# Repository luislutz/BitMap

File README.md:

# BitMap
Multifunction Eurorack Module with 8 Bit parallel ADC and DAC in the Heart. Main selling points:
- most versatile Bitcrusher in Eurorack with passive LPF
- infinite Sample and Hold with slew, works with 1v/oct pitch CV!
- Halftone Chromatic, Chromatic and weird scales Quantizer (every 2nd, 4th, 8th, 16th)
- inspiring Drum/Gate Sequencer with 8 Channels
- VCA and Ringmodulator
- White Noise, 8 types of digital noise and processed White Noise (Bitcrushed, Sample Rate reduced and Filtered to your taste)

## Features and Functions:

Conversion of analog voltage in 8 Bit digital value
Possibility of swapping individual bits and switching them off manually, 
aswell as removing the bits in order via the voltage controlled Bitcrush-Knob
Reconversion of digital 8 Bit value in analog voltage

ADC and DAC can be used as seperate units with the same clock (onboard pulsegenerator or external trigger/gates):

ADC: 1 analog input, 8 digital bit outputs derived from the input voltage (Gates), additional Clip output wich goes high when the input voltage is bigger than the ADC range, this produces hard clipping

DAC: 8 digital inputs (Gates), 1 analog output derived from the digital input values. Possibitlity to set the refence voltage of the DAC externally via an analog gain input, works as a VCA with unipolar Voltage or Ringmodulator with bipolar Voltage

Normalled white noise to the analog input of the ADC aswell as a seperate unprocessed noise output. This gives direct access to 9 flavours of Digital Noise at the ADC Bit outputs and Clip output and a processed white noise at the analog output of the DAC without having to add some other modules or cables. The processed white noise can of course be bitcrushed and samplerate reduced as you wish aswell. Random Voltages in S and Hold style are achievable too with really slow clock rate. With the passive Slew limiter (LPF) at the output the noise can be filtered too and it is possible to slew the Sample and Hold Voltages.

Because the value of the incoming analog voltage is stored in Digital realm. The module does act as a Sample and Hold circuit with infinite holding time and zero voltage drop. Using this module to sample and hold pitch CV is no problem.

The coolest feature by far is the precise mapping of the 256 steps in 8 Bit to the V/Oct scale at the analog input and output. To set the module up for quantizing Pitch CV, just turn the input and output level knobs all the way up. Now a Voltage of 0 (C3) at the input equals a digital word of 10000000, C#3 would be 10000010, D3 = 10000100, D#3 = 10000110 and so on. one Sem,itone equals two steps in the Digital realm. So the minimum voltage value will be -5.33V (00000000, G#-3) and the maximum voltage is 5.25 (11111110, D#8). The Quantizing range is therefor over 10 Octaves of Notes. There are many possibilities for quantizing pitch cv. For Chromatic quantizing, disable the lowest value bit. if you want everey 2nd, 4th, 8th semitone and so on,disable more bits or make any weird combination of bits to make weird scales that are impossible using a normal quantizer. Normal scales like Major Minor or Phrigyian are not so easy to replicate with this module.

## Different Use Cases:

- Voltage controlled Bitreducing of CV and Audio signals
- Voltage controlled Reducing of Sample Rate for CV and Audio Signals (S&H)
- Random Voltage and Gate Source
- Sequencing Drums with mutes (up to 9 channels)
- Quantizing of pitch CV (Chromatic and unusal scales)
- VCA and Ringmodulator (after AD->DA Conversion on the Output)
- Sequencer for pitch CV
- infinite Sample and Hold with external trigger
- Pitch Sequence Transformation to related, but different Sequences
- Slew and Low pass filtering of output with switchable range (passive)
- Strange Wavefolder (swapping or switching individula bits of Audio)
- Distortion (hardclipping at 10vpp)
- Noise source (1 unprocessed Noise white noise outoput, 9 times digital noise with different flavours, and one 8 bit white noise processable with Bitmap as you wish) 
- Compatible with Leibniz system from Xaoc via Leibniz headers on the back of the module!

## Building Instructions:

This is no easy build! Althought it is mostly throughhole, the Module is really packed with Components and ICs.
The hardest part is to solder the 0603 SMD Resistors and keep them unharmed during the rest of the soldering

Start with the 0603 SMD resistors on the backside of the front PCB!

Using Leibniz Subsystem:
There are 9 Jumpers on the front PCB. if you solder these jumpers, the optional connectors for the Leibniz subsystem are bridged and wont be needed anymore. If you want to use the Leibniz subsystem now or in the Future, please make sure you dont solder the jumpers and solder the connectors for the Leibniz subsystem.
Before soldering the Thonkiconn Jacks (3.5mm mono jacks) make sure to solder the Leibniz Headers first. Make sure the pins of the Leibniz connector is flush with the Frontside of the PCB, that way they dont interfere with the 3.5mm Mono Jacks on the oter side of the PCB.

After you have made your decision, start putting everything else in by starting with the most slim parts (Resistors, diodes) and end with the Biggest parts (Elko Caps, trimmers, pin headers)
Solder the panel components with the panel already mounted on them to make sure the parts will align with the holes in the PCB Panel

## Calibraton:

Set Up: 
- SampleRate Knob ~70% to the right
- Bitcrush Knob 100% to the left
- Input Level Knob 100% to the left
- CV Scale Knob 100% to the left
- Slew Pot 100% to the left
- Output Pot 100% to the right
- All individual Bit Buttons are not pressed, e.g. Bits are all active!

there are 6 calibrating trimpotentiometers in total to be adjusted:

1. Input Offset trim RV5 10K:
Turn the Input Level Knob on the Panel completely to the left first. Listen to the Noise Output Jack. Turn the Noise Trim Potentiometer completely down, so that there is absolutely no Nosie left at the Noise Output Jack. This should result in less flickering of the Bit LEDS on the Panel (This is really important). Now youre set for precise calibration. Adjust the Input Offset Trim Potentiometer so that the LEDs light up with this pattern from left to right without flickering: 00000001 (EG Only BIT8 is set active)

2. Input Scale trim RV4 10K:
Take a constant voltage source with exactly 5V (coming from a sequencer or similar) and plug it in the analog voltage input. Turn the Input Level Knob on the Frontpanel completely up (100% to the right). Adjust the Input Scale Trim Potentiometer so that LEDs light up with this pattern from left to right: 00011111    ---> repeat Step 1. and Step 2. until it stays at the correct LED-Pattern with the corresponding input voltage and no jitter.

3. Output Offset trim RV6 2K:
Keep the precise 5V source plugged in. Turn the Input Level Knob on the panel to zero again. Connect the output to a Voltage Meter or to the V/Oct input of an Oscillator that is already well calibrated to 1V/Oct. Make sure you see the Pattern 00000001 on the LEDs. Adjust the Output Offset Trim until the Output Voltage equals excactly 0V or your oscillator doesnt change pitch when unpluuging the cable from the V/Oct input (should be the case for a good calibrated VCO with 0V at the cable)

4. Output Scale trim RV9 2K:
Keep the precise 5V source plugged in. Turn the Input Voltage Knob on the Panel to max (100% to the right). Now the LED-Pattern should be (00011111) again. Leave the Analog Voltage Output connected to the oscillator or the Voltage Meter. Adjust the Output Scale Trim until the output matcehs excactly 5 volts or the Oscillator is playing 5 Octaves above when compared to Step 3.
--> your Input and Output Scales and Offsets are now set correctly to 1V/Oct

5. Max Sample Rate trim RV12 2K:
Feed a Sinewave into the analog input Jack. Listen to the output of the Module. Turn the Sample Rate Knob on the panel to max value (100% to the right). Adjust the Sample Rate Trim to minimal noise on the output (Hint: if the sample rate just exceeds audible range its perfect there). if the Sample Rate trim is set to high. The ADC stalls when turning the SR pot all the way to the Right, you can unstall the ADC by turning it quite down, but its better to set that trimmer in a way that the ADC doest lock at all when the Sample Rate Pot is at its max Setting (100% to the right)

6. Noise Level trim RV3 100K: 
Turn the Input Level Knob again completely to the left. Now turn the Noise trimpot up until there is a slight flickering at the LEDs on the Panel (because the dac is very quickly switching States because of increased signal noise at the input). Turn it slightly back so that the flickering stops. Noise level is now set to Max Level without interference to the input Voltage. Any higher and the Readings of Voltages to the Analog Voltage input get inprecise and noisy. For max precision on Pitch CV you can even turn the noise trim completely down :) if your more after noisy behaviour it doesnt matter that much and you can turn up the noise quite abit :D

if you have any questions regarding the building or calibration Process you can write me an email to luis.lutz95@gmail.com 

Thanks for thaking the challenge to build one of these!!!

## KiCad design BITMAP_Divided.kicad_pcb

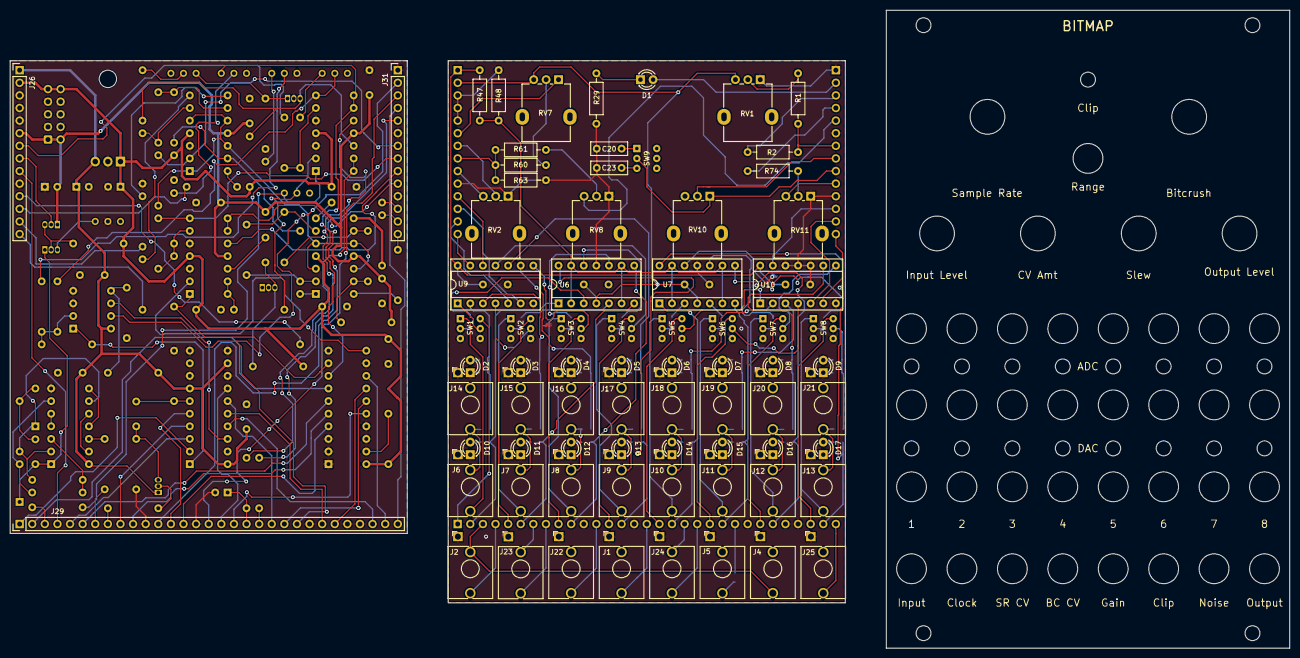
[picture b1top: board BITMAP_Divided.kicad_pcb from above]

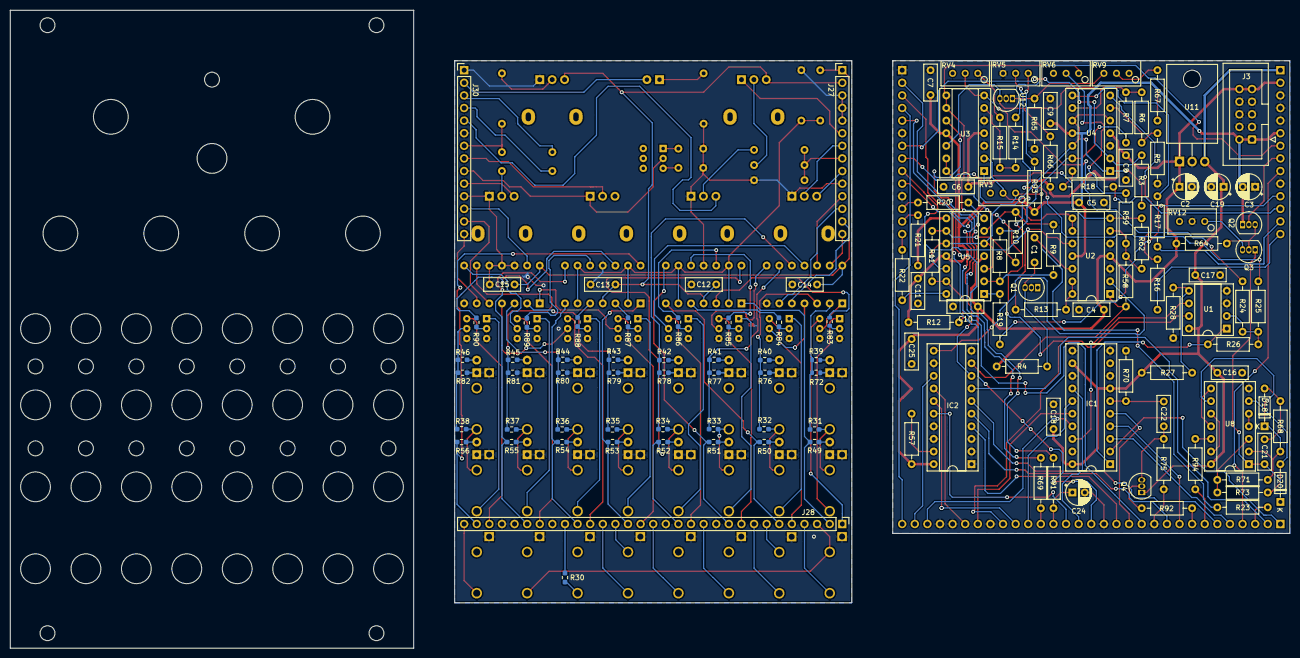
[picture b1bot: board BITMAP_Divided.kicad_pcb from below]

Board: 2 copper layers, 257.8 x 128.5 mm, 208 parts (134 on the bottom side), 217 nets.

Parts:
C1, C4, C5, C6, C7, C8, C9, C10, C11, C12, C13, C14, C15, C16, C17, C18, C25: 100n; C_Rect_L7.2mm_W2.5mm_P5.00mm_FKS2_FKP2_MKS2_MKP2
C2, C3, C19, C24: 10u; CP_Radial_D5.0mm_P2.50mm
C20: 68n; C_Rect_L7.2mm_W2.5mm_P5.00mm_FKS2_FKP2_MKS2_MKP2
C21: 2.2n; C_Rect_L7.2mm_W2.5mm_P5.00mm_FKS2_FKP2_MKS2_MKP2
C22: 1n; C_Rect_L7.2mm_W2.5mm_P5.00mm_FKS2_FKP2_MKS2_MKP2
C23: 680n; C_Rect_L7.2mm_W2.5mm_P5.00mm_FKS2_FKP2_MKS2_MKP2
D1, D2, D3, D4, D5, D6, D7, D8, D9, D10, D11, D12, D13, D14, D15, D16, D17: LED; LED_D3.0mm
D18, D20: 1N4148; D_DO-35_SOD27_P7.62mm_Horizontal
IC1: ADC0820CCN; DIP-20_W7.62mm_Socket
IC2: DAC0830LJ; DIP-20_W7.62mm_Socket
J1: Bitcrush CV; Jack_3.5mm_QingPu_WQP-PJ398SM_Vertical_CircularHoles
J2: Signal Input; Jack_3.5mm_QingPu_WQP-PJ398SM_Vertical_CircularHoles
J3: Eurorack Power Header; IDC-Header_2x05_P2.54mm_Vertical
J4: Noise Output; Jack_3.5mm_QingPu_WQP-PJ398SM_Vertical_CircularHoles
J5: Clip Output; Jack_3.5mm_QingPu_WQP-PJ398SM_Vertical_CircularHoles
J6: Bit 0 Input; Jack_3.5mm_QingPu_WQP-PJ398SM_Vertical_CircularHoles
J7: Bit 1 Input; Jack_3.5mm_QingPu_WQP-PJ398SM_Vertical_CircularHoles
J8: Bit 2 Input; Jack_3.5mm_QingPu_WQP-PJ398SM_Vertical_CircularHoles
J9: Bit 3 Input; Jack_3.5mm_QingPu_WQP-PJ398SM_Vertical_CircularHoles
J10: Bit 4 Input; Jack_3.5mm_QingPu_WQP-PJ398SM_Vertical_CircularHoles
J11: Bit 5 Input; Jack_3.5mm_QingPu_WQP-PJ398SM_Vertical_CircularHoles
J12: Bit 6 Input; Jack_3.5mm_QingPu_WQP-PJ398SM_Vertical_CircularHoles
J13: Bit 7 Input; Jack_3.5mm_QingPu_WQP-PJ398SM_Vertical_CircularHoles
J14: Bit 0 Output; Jack_3.5mm_QingPu_WQP-PJ398SM_Vertical_CircularHoles
J15: Bit 1 Output; Jack_3.5mm_QingPu_WQP-PJ398SM_Vertical_CircularHoles
J16: Bit 2 Output; Jack_3.5mm_QingPu_WQP-PJ398SM_Vertical_CircularHoles
J17: Bit 3 Output; Jack_3.5mm_QingPu_WQP-PJ398SM_Vertical_CircularHoles
J18: Bit 4 Output; Jack_3.5mm_QingPu_WQP-PJ398SM_Vertical_CircularHoles
J19: Bit 5 Output; Jack_3.5mm_QingPu_WQP-PJ398SM_Vertical_CircularHoles
J20: Bit 6 Output; Jack_3.5mm_QingPu_WQP-PJ398SM_Vertical_CircularHoles
J21: Bit 7 Output; Jack_3.5mm_QingPu_WQP-PJ398SM_Vertical_CircularHoles
J22: Sample Rate CV; Jack_3.5mm_QingPu_WQP-PJ398SM_Vertical_CircularHoles
J23: Ext Clock Input; Jack_3.5mm_QingPu_WQP-PJ398SM_Vertical_CircularHoles
J24: External Voltage Reference Input; Jack_3.5mm_QingPu_WQP-PJ398SM_Vertical_CircularHoles
J25: Signal Output; Jack_3.5mm_QingPu_WQP-PJ398SM_Vertical_CircularHoles
J26, J31: Conn_01x14_Male; PinHeader_1x14_P2.54mm_Vertical
J27, J30: Conn_01x14_Female; PinHeader_1x14_P2.54mm_Vertical
J28: Conn_01x31_Female; PinHeader_1x31_P2.54mm_Vertical
J29: Conn_01x31_Male; PinHeader_1x31_P2.54mm_Vertical
Q1, Q3, Q4: BC547; TO-92_Inline
Q2: BC557; TO-92_Inline
R1, R3, R15: 100K; R_Axial_DIN0207_L6.3mm_D2.5mm_P10.16mm_Horizontal
R2, R60, R61: 47K; R_Axial_DIN0207_L6.3mm_D2.5mm_P10.16mm_Horizontal
R4: 200K; R_Axial_DIN0207_L6.3mm_D2.5mm_P10.16mm_Horizontal
R5, R6, R7, R8, R9, R10, R11, R12, R16, R17, R18, R19, R20, R21, R22: 5.1K; R_Axial_DIN0207_L6.3mm_D2.5mm_P10.16mm_Horizontal
R13, R23, R29, R69, R75, R92, R94: 1K; R_Axial_DIN0207_L6.3mm_D2.5mm_P10.16mm_Horizontal
R14: 220K; R_Axial_DIN0207_L6.3mm_D2.5mm_P10.16mm_Horizontal
R24, R25, R26, R27, R28, R47, R48, R57, R58, R65, R66, R67, R70, R71, R91: 10K; R_Axial_DIN0207_L6.3mm_D2.5mm_P10.16mm_Horizontal
R30, R31, R32, R33, R34, R35, R36, R37, R38, R40, R41, R42, R43, R44, R45, R46, R49, R50, R51, R52, R53, R54, R55, R56, R84, R85, R86, R87, R88, R89, R90: 1K; R_0603_1608Metric_Pad0.98x0.95mm_HandSolder
R39, R83: 1K; R_0603_1608Metric
R59, R62: 20K; R_Axial_DIN0207_L6.3mm_D2.5mm_P10.16mm_Horizontal
R63: 1.8K; R_Axial_DIN0207_L6.3mm_D2.5mm_P10.16mm_Horizontal
R64: 1M; R_Axial_DIN0207_L6.3mm_D2.5mm_P10.16mm_Horizontal
R68: 680R; R_Axial_DIN0207_L6.3mm_D2.5mm_P10.16mm_Horizontal
R72: 10K; R_0603_1608Metric
R73: 22K; R_Axial_DIN0207_L6.3mm_D2.5mm_P10.16mm_Horizontal
R74: 470R; R_Axial_DIN0207_L6.3mm_D2.5mm_P10.16mm_Horizontal
R76, R77, R78, R79, R80, R81, R82: 10K; R_0603_1608Metric_Pad0.98x0.95mm_HandSolder
R93: 33K; R_Axial_DIN0207_L6.3mm_D2.5mm_P10.16mm_Horizontal
RV1, RV2, RV7, RV8, RV11: 100K; Potentiometer_Alpha_RD901F-40-00D_Single_Vertical
RV3: 100K; Potentiometer_Bourns_3296W_Vertical
RV4, RV5: 10K; Potentiometer_Bourns_3296W_Vertical
RV6, RV9, RV12: 2K; Potentiometer_Bourns_3296W_Vertical
RV10: 10K; Potentiometer_Alpha_RD901F-40-00D_Single_Vertical
SW1: Bit 0 Mute Switch; 7x7Switch
SW2: Bit 1 Mute Switch; 7x7Switch
SW3: Bit 2 Mute Switch; 7x7Switch
SW4: Bit 3 Mute Switch; 7x7Switch
SW5: Bit 4 Mute Switch; 7x7Switch
SW6: Bit 5 Mute Switch; 7x7Switch
SW7: Bit 6 Mute Switch; 7x7Switch
SW8: Bit 7 Mute Switch; 7x7Switch
SW9: Slew Range Switch; 7x7Switch
U1: MCP6002-xP; DIP-8_W7.62mm_Socket
U2, U3, U4, U5: TL074; DIP-14_W7.62mm_Socket
U6, U7: LM324; DIP-14_W7.62mm_Socket
U8: 4069; DIP-14_W7.62mm_Socket
U9, U10: 4066; DIP-14_W7.62mm_Socket
U11: L7805; TO-220-3_Horizontal_TabDown
U12: TL431LP; TO-92_Inline

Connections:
+5V_Back: C16.1, C17.1, C18.2, C19.1, IC1.7, IC1.12, IC1.20, J26.1, Q4.1, R27.2, U1.8, U8.14, U11.3
+5V_Front: C14.1, C15.1, J27.1, R47.2, U9.14, U10.14
+12V_Back: C2.1, C4.1, C6.1, C8.1, C10.1, C25.2, IC2.20, J3.9, J3.10, J26.2, R4.2, R57.2, R64.2, R66.2, U2.4, U3.4, U4.4, U5.4, U11.1
+12V_Front: C12.1, C13.1, J27.2, RV1.3, RV7.3, U6.4, U7.4
-12V_Back: C3.2, C5.2, C7.2, C9.2, C11.2, J3.1, J3.2, J26.6, Q2.1, R12.1, R93.2, U2.11, U3.11, U4.11, U5.11
-12V_Front: J27.6, RV7.1
B0_Back: IC2.7, J29.2
B0_Front: J28.2, R49.2, U6.1
B1_Back: IC2.6, J29.6
B1_Front: J28.6, R50.2, U6.7
B2_Back: IC2.5, J29.10
B2_Front: J28.10, R51.2, U6.8
B3_Back: IC2.4, J29.14
B3_Front: J28.14, R52.2, U6.14
B4_Back: IC2.16, J29.18
B4_Front: J28.18, R53.2, U7.1
B5_Back: IC2.15, J29.22
B5_Front: J28.22, R54.2, U7.7
B6_Back: IC2.14, J29.26
B6_Front: J28.26, R55.2, U7.8
B7_Back: IC2.13, J29.30
B7_Front: J28.30, R56.2, U7.14
Bitcrush_Back: J31.7, R3.2, U4.2
Bitcrush_Back_Jack1: J29.16, J31.3
Bitcrush_Front: J30.7, R1.1, R2.1
Bitcrush_Front_Jack1: J1.2, J28.16
Bitcrush_Front_Jack2: J30.3, R2.2
Clip_Back: J29.23, J31.2, U1.7
Clip_Front_Jack: J28.23, R30.1
Clip_Front_LED: D1.2, J30.2
Clk: C22.2, IC1.6, R70.2
Clock1_Back: J29.7, R94.1
Clock1_Front: J23.3, J28.7
Clock2_Back: J29.8, R92.1
Clock2_Front: J23.2, J28.8
D0_Back: IC1.2, J29.1
D0_Front: J28.1, SW1.4
D1_Back: IC1.3, J29.5
D1_Front: J28.5, SW2.4
D2_Back: IC1.4, J29.9
D2_Front: J28.9, SW3.4
D3_Back: IC1.5, J29.13
D3_Front: J28.13, SW4.4
D4_Back: IC1.14, J29.17
D4_Front: J28.17, SW5.4
D5_Back: IC1.15, J29.21
D5_Front: J28.21, SW6.4
D6_Back: IC1.16, J29.25
D6_Front: J28.25, SW7.4
D7_Back: IC1.17, J29.29
D7_Front: J28.29, SW8.4
GND_Back: C2.2, C3.1, C4.2, C5.1, C6.2, C7.1, C8.2, C9.1, C10.2, C11.1, C16.2, C17.2, C18.1, C19.2, C24.2, C25.1, IC1.8, IC1.10, IC1.11, IC1.13, IC2.1, IC2.2, IC2.3, IC2.10, IC2.12, IC2.17, IC2.18, J3.3, J3.4, J3.5, J3.6, J3.7, J3.8, J26.3, J26.4, J26.5, J26.10, J29.11, J29.15, J29.24, J29.27, J29.28, J31.1, J31.6, J31.11, Q1.2, R5.2, R28.1, R65.1, R70.1, R75.2, RV5.3, RV12.2, U1.3, U1.4, U2.3, U2.5, U3.3, U3.5, U4.3, U8.7, U11.2, U12.2
GND_Front: C12.2, C13.2, C14.2, C15.2, C20.2, C23.2, D2.1, D3.1, D4.1, D5.1, D6.1, D7.1, D8.1, D9.1, D10.1, D11.1, D12.1, D13.1, D14.1, D15.1, D16.1, D17.1, J1.1, J2.1, J4.1, J5.1, J6.1, J7.1, J8.1, J9.1, J10.1, J11.1, J12.1, J13.1, J14.1, J15.1, J16.1, J17.1, J18.1, J19.1, J20.1, J21.1, J22.1, J23.1, J24.1, J25.1, J27.3, J27.4, J27.5, J27.10, J28.11, J28.15, J28.24, J28.27, J28.28, J30.1, J30.6, J30.11, R29.2, R48.1, R63.1, R72.1, R76.1, R77.1, R78.1, R79.1, R80.1, R81.1, R82.1, RV1.1, RV2.1, RV8.1, RV11.1, SW1.3, SW1.6, SW2.3, SW2.6, SW3.3, SW3.6, SW4.3, SW4.6, SW5.3, SW5.6, SW6.3, SW6.6, SW7.3, SW7.6, SW8.3, SW8.6, U6.11, U7.11, U9.7, U10.7, U10.10, U10.11, U10.12
In_Back: J26.7, R14.2
In_Back1: J26.9, J29.4
In_Front: J27.7, RV2.2
In_Front1: J2.2, J28.4
In_Front2: J27.9, RV2.3
unnamed: C1.1, Q1.3, R4.1
unnamed: C1.2, U2.12
unnamed: C20.1, SW9.1
unnamed: C21.1, D20.1, Q3.1, U8.1
unnamed: C21.2, D18.2, R68.2
unnamed: C22.1, Q4.3, R75.1
unnamed: C23.1, SW9.3
unnamed: D1.1, R29.1
unnamed: D2.2, R39.1
unnamed: D3.2, R40.1
unnamed: D4.2, R41.1
unnamed: D5.2, R42.1
unnamed: D6.2, R43.1
unnamed: D7.2, R44.1
unnamed: D8.2, R45.1
unnamed: D9.2, R46.1
unnamed: D10.2, R49.1
unnamed: D11.2, R50.1
unnamed: D12.2, R51.1
unnamed: D13.2, R52.1
unnamed: D14.2, R53.1
unnamed: D15.2, R54.1
unnamed: D16.2, R55.1
unnamed: D17.2, R56.1
unnamed: D18.1, R68.1, R71.2, U8.2, U8.9
unnamed: D20.2, R73.1, U8.6
unnamed: IC1.1, R26.1, U1.1
unnamed: IC1.18, U1.6
unnamed: IC2.9, R58.2, U2.1
unnamed: IC2.11, U2.2
unnamed: IC2.19, R57.1
unnamed: J5.2, R30.2
unnamed: J6.2, SW1.1
unnamed: J7.2, SW2.1
unnamed: J8.2, SW3.1
unnamed: J9.2, SW4.1
unnamed: J10.2, SW5.1
unnamed: J10.3, J18.2, R35.1
unnamed: J11.2, SW6.1
unnamed: J11.3, J19.2, R36.1
unnamed: J12.2, SW7.1
unnamed: J12.3, J20.2, R37.1
unnamed: J13.2, SW8.1
unnamed: J13.3, J21.2, R38.1
unnamed: J6.3, J14.2, R31.1
unnamed: J7.3, J15.2, R32.1
unnamed: J8.3, J16.2, R33.1
unnamed: J9.3, J17.2, R34.1
unnamed: Q2.3, Q3.2, R64.1
unnamed: Q3.3, RV12.1
unnamed: Q4.2, R92.2
unnamed: R1.2, RV1.2
unnamed: R3.1, U4.1, U4.5, U4.10, U4.12, U5.3, U5.5, U5.10, U5.12
unnamed: R5.1, R6.2, U4.6
unnamed: R6.1, R7.2, U4.9
unnamed: R7.1, R8.2, U4.13
unnamed: R8.1, R9.2, U5.2
unnamed: R10.1, R11.2, U5.9
unnamed: R9.1, R10.2, U5.6
unnamed: R11.1, R12.2, U5.13
unnamed: R13.1, RV3.2, U3.2
unnamed: R13.2, U2.13, U2.14
unnamed: R14.1, R15.2, U3.6
unnamed: R15.1, RV4.1
unnamed: R16.2, U4.7
unnamed: R17.2, U4.8
unnamed: R18.2, U4.14
unnamed: R19.2, U5.1
unnamed: R20.2, U5.7
unnamed: R21.2, U5.8
unnamed: R22.2, U5.14
unnamed: R23.2, RV3.1, U3.1
unnamed: R24.1, R25.1, R26.2, U1.2
unnamed: R24.2, RV4.2, U3.7
unnamed: R25.2, RV5.2
unnamed: R27.1, R28.2, U1.5
unnamed: R31.2, R39.2, R72.2, U9.2
unnamed: R32.2, R40.2, R76.2, U9.3
unnamed: R33.2, R41.2, R77.2, U9.9
unnamed: R34.2, R42.2, R78.2, U9.10
unnamed: R35.2, R43.2, R79.2, U10.2
unnamed: R36.2, R44.2, R80.2, U10.3
unnamed: R37.2, R45.2, R81.2, U10.9
unnamed: R38.2, R46.2, R82.2, SW8.5
unnamed: R47.1, R48.2, U6.2, U6.6, U6.9, U6.13, U7.2, U7.6, U7.9, U7.13
unnamed: R58.1, R59.1, R62.2, U2.6
unnamed: R59.2, RV6.2
unnamed: R60.2, RV7.2
unnamed: R61.2, RV8.2
unnamed: R65.2, RV9.3, U12.1
unnamed: R66.1, R67.2, U3.12, U12.3
unnamed: R67.1, RV9.2
unnamed: R69.1, U3.10
unnamed: R71.1, R73.2, U8.3
unnamed: R74.2, RV11.2
unnamed: R83.1, U6.3
unnamed: R83.2, SW1.2
unnamed: R84.1, U6.5
unnamed: R84.2, SW2.2
unnamed: R85.1, U6.10
unnamed: R85.2, SW3.2
unnamed: R86.1, U6.12
unnamed: R86.2, SW4.2
unnamed: R87.1, U7.3
unnamed: R87.2, SW5.2
unnamed: R88.1, U7.5
unnamed: R88.2, SW6.2
unnamed: R89.1, U7.10
unnamed: R89.2, SW7.2
unnamed: R90.1, U7.12
unnamed: R90.2, SW8.2
unnamed: R91.2, U3.13, U3.14
unnamed: R93.1, RV5.1
unnamed: R94.2, U8.12
unnamed: SW1.5, U9.1
unnamed: SW2.5, U9.4
unnamed: SW3.5, U9.8
unnamed: SW4.5, U9.11
unnamed: SW5.5, U10.1
unnamed: SW6.5, U10.4
unnamed: SW7.5, U10.8
unnamed: U8.4, U8.5
unnamed: U8.10, U8.13
unnamed: U8.8, U8.11
Noise_Back: J29.3, R23.1
Noise_Front: J2.3, J4.2, J28.3
Out1_Back: J31.8, R62.1, U2.7
Out1_Front: J30.8, RV10.2
Out2_Back: J31.9, U2.10
Out2_Front: J30.9, RV10.1, SW9.2
Out3_Back: J31.10, U2.8, U2.9
Out3_Front: J30.10, RV11.3
Out4_Back: J29.31, J31.4
Out4_Front: J30.4, R74.1
Out5_Front: J25.2, J28.31
Rate_Back: J26.8, Q2.2
Rate_Front: J27.8, R60.1, R61.1, R63.2
Ref1_Back: C24.1, J29.19, R91.1
Ref1_Front: J24.3, J28.19
Ref2_Back: J29.20, R69.2
Ref2_Front: J24.2, J28.20
S0_Back: J26.14, R16.1
S0_Front: J27.14, U9.13
S1_Back: J26.13, R17.1
S1_Front: J27.13, U9.5
S2_Back: J26.12, R18.1
S2_Front: J27.12, U9.6
S3_Back: J26.11, R19.1
S3_Front: J27.11, U9.12
S4_Back: J31.12, R20.1
S4_Front: J30.12, U10.13
S5_Back: J31.13, R21.1
S5_Front: J30.13, U10.5
S6_Back: J31.14, R22.1
S6_Front: J30.14, U10.6
SR_Jack1_Back: J29.12, J31.5
SR_Jack1_Front: J22.2, J28.12
SR_Jack2_Front: J30.5, RV8.3
Vref: IC2.8, RV6.1, U3.8, U3.9

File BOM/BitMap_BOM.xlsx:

Part number on Schematic | Value | Amount | Package | Link for ordering | Comment
Resistors SMD
R31, R32, R33, R34, R35, R36, R37, R38, R83, R83, R85, R86, R87, R88, R89, R90 | 1K | 16 | 0603 SMD | 1K Ohm 1/10W 1% 0603 SMD Chip Resistors (taydaelectronics.com)
R72, R76, R77, R78, R79, R80, R81, R82 | 10K | 8 | 0603 SMD | 10K Ohm 1/10W 1% 0603 SMD Chip Resistors (taydaelectronics.com)
R39, R40, R41, R42, R43, R44, R45, R46 | LED resistors ADC ~3.3K | 8 | 0603 SMD | 4.7K Ohm 1/10W 1% 0603 SMD Chip Resistors (taydaelectronics.com) | Resitor for setting the brightness on the ADC LEDs Running on 5V. Recommended v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
R49, R50, R51. R52, R53, R54, R55, R56 | LED resistors DAC ~75K | 8 | 0603 SMD | 100K Ohm 1/10W 1% 0603 SMD Chip Resistors (taydaelectronics.com) | Resitor for setting the brightness on the DAC LEDs. Running on 12V. Recommended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
Resistors THT
R74 | 470R | 1 | THT 1/4W | Save time Easy Ordering Page for 1/4W 1% Resistors (taydaelectronics.com)
R68 | 680R | 1 | THT 1/4W | Save time Easy Ordering Page for 1/4W 1% Resistors (taydaelectronics.com)
R70, R15, R23, R29, R30, R69, R92, R94 | 1K | 9 | THT 1/4W | Save time Easy Ordering Page for 1/4W 1% Resistors (taydaelectronics.com) | R29 is the Resistor which sets the brightness of the Clip LED running on 5V. Re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
R63 | 1.8K | 1 | THT 1/4W | Save time Easy Ordering Page for 1/4W 1% Resistors (taydaelectronics.com)
R5, R6, R7, R8, R9, R10, R11, R12, R16, R17, R18, R19, R20, R21, R22 | 5.1K | 15 | THT 1/4W | Save time Easy Ordering Page for 1/4W 1% Resistors (taydaelectronics.com)
R24, R26, R25, R27, R28, R47, R48, R57, R58, R65, R66, R67, R71, R75, R91, R93 | 10K | 16 | THT 1/4W | Save time Easy Ordering Page for 1/4W 1% Resistors (taydaelectronics.com)
R59, R62 | 20K | 2 | THT 1/4W | Save time Easy Ordering Page for 1/4W 1% Resistors (taydaelectronics.com)
R73 | 22K | 1 | THT 1/4W | Save time Easy Ordering Page for 1/4W 1% Resistors (taydaelectronics.com)
R2, R60, R61 | 47K | 3 | THT 1/4W | Save time Easy Ordering Page for 1/4W 1% Resistors (taydaelectronics.com)
R15 | 91K | 1 | THT 1/4W | Save time Easy Ordering Page for 1/4W 1% Resistors (taydaelectronics.com)
R1, R3, R95, | 100K | 3 | THT 1/4W | Save time Easy Ordering Page for 1/4W 1% Resistors (taydaelectronics.com)
R4, | 200k | 1 | THT 1/4W | Save time Easy Ordering Page for 1/4W 1% Resistors (taydaelectronics.com)
R14 | 220K | 1 | THT 1/4W | Save time Easy Ordering Page for 1/4W 1% Resistors (taydaelectronics.com)
R64 | 1M | 1 | THT 1/4W | Save time Easy Ordering Page for 1/4W 1% Resistors (taydaelectronics.com)
Capacitors
C4, C5, C6, C7, C8, C9, C10, C11, C12, C13, C14, C15, C16, C17, C18, C25 | 100n | 16 | Ceramic | https://www.taydaelectronics.com/100nf-50v-multilayer-monoli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
C21 | 22n | 1 | Film | 22nF 0.022uF 100V 5% Polyester Film Box Type Capacitor (taydaelectronics.com)
C20 | 68n | 1 | Film | 68nF 0.068uF 100V 5% Polyester Film Box Type Capacitor (taydaelectronics.com)
C1 | 100n | 1 | Film | 100nF 0.1uF 100V 5% Polyester Film Box Type Capacitor (taydaelectronics.com)
C23 | 680n | 1 | Film | 680nF 0.68uF 100V 5% Polyester Film Box Type Capacitor (taydaelectronics.com)
C2, C3, C19, C24 | 10u | 4 | Elko | 10uF 50V 105C Radial Electrolytic Capacitor 5x11mm (taydaelectronics.com)
Diodes
D1 | Clip LED | 1 | LED 3mm round | LED 3mm Red Water Clear Ultra Bright (taydaelectronics.com)
D2, D3, D4, D5, D6, D7, D8, D9 | LEDs ADC | 8 | LED 3mm round | LED 3mm Orange Water Clear (taydaelectronics.com) | Tayda has no yellow LEDs at the moment….
D10, D11, D12, D13, D14, D15, D16, D17 | LEDs DAC | 8 | LED 3mm round | LED 3mm Green Water Clear Super Bright (taydaelectronics.com)
D19 | BAT43 | 1
D18, D20 | 1N4148 | 2 |  | 1N4148 Switching Signal Diode (taydaelectronics.com)
Variable Resistors
RV3 | 100K | 1 | Trim | 100K OHM TRIMMER POTENTIOMETER CERMET 25 TURNS 3296W (taydaelectronics.com)
RV6, RV9, RV12 | 2K | 3 | Trim | 2K OHM CERMET TRIMMER POTENTIOMETER 25 TURNS 3296W (taydaelectronics.com)
RV4, RV5, RV14 | 10K | 3 | Trim | 10K OHM TRIMMER POTENTIOMETER CERMET 25 TURNS 3296W (taydaelectronics.com)
RV10 | 10K Knurled Shaft | 1 | Pot | 10K OHM Linear Taper Potentiometer Spline Shaft PCB Mount 9mm (taydaelectronics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 | linear Taper
RV2, RV11, RV8 | 100K Knurled Shaft | 3 | Pot | 100K OHM Linear Taper Potentiometer Spline Shaft PCB Mount 9mm (taydaelectronic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 | linear Taper
RV1, RV7 | 100K Round Shaft | 2 | Pot | 100K OHM Linear Taper Potentiometer Round Shaft PCB 9mm (taydaelectronics.com) | linear Taper
Transistors
Q1, Q3, Q4 | BC547 | 3 | TO-92 | BC547 Transistor NPN 45V 0.1A (taydaelectronics.com)
Q2 | BC557 | 1 | TO-92 | BC557 Transistor PNP 45V 0.1A TO-92 BC557B-KEC/P (taydaelectronics.com)
Jacks and Connections
J1, J2, J4, J5, J6, J7, J8, J9, J10, J11, J12, J13, J14, J15, J16, J17, J18, J1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 | Thonkiconn type Mono Jack | 24 |  | PJ-3001F 3.5mm Mono Phone Jack (taydaelectronics.com)
J3 | Pin Header 2x5 Male Boxed | 1 |  | 10 Pin Box Header Connector 2.54mm (taydaelectronics.com)
J32, J33 | Pin Header 2x5 Male P2.54 | 2
J27, J30 | Pin Header 1x14 Female | 2 |  | 40 Pin 2.54 mm Single Row Female Pin Header (taydaelectronics.com) | Cut to lenght!
J26, J31 | Pin Header 1x14 Male | 2 |  | 40 Pin 2.54 mm Single Row Pin Header Strip (taydaelectronics.com) | Cut to lenght!
J28 | Pin Header 1x31 Female | 1 |  | 40 Pin 2.54 mm Single Row Female Pin Header (taydaelectronics.com) | Cut to lenght!
J29 | Pin Header 1x31 Male | 1 |  | 40 Pin 2.54 mm Single Row Pin Header Strip (taydaelectronics.com) | Cut to lenght!
Switches
S1, S2, S3, S4, S5, S6, S7, S8, S9 | DPDT latching switch 7x7mm | 9 |  | PUSH BUTTON SWITCH DC 30V 0.1A DPDT 7x7mm (taydaelectronics.com)
Integrated Circuits
U1 | MCP6002 | 1 | DIP-8
U2, U3, U4, U5 | TL074 | 4 | DIP-14 | TL074 Quad Operational Amplifier J-FET PDIP-14 TL074CN (taydaelectronics.com)
U8 | CD4069 | 1 | DIP-14 | CD4069UBE CD4069 4069 Hex Inverter IC (taydaelectronics.com)
U6, U7 | LM324 | 2 | DIP-14 | LM324N LM324 324 Low Power Quad Op-Amp IC (taydaelectronics.com)
U9, U10 | CD4066 | 2 | DIP-14 | CD4066 4066 IC CMOS QUAD BILATERAL SWITCH (taydaelectronics.com)
U11 | L7805 | 1 | TO-220-3 | LM7805 L7805 7805 Voltage Regulator IC 5V 1.5A (taydaelectronics.com)
U12 | TL431 | 1 | TO-92 | TL431ACL TL431 PRECISION SHUNT REGULATOR (taydaelectronics.com)
IC1 | ADC0820CCN | 1 | DIP-20
IC2 | DAC0830LJ | 1 | DIP-20
IC - Sockets
E1 | IC Socket | 1 | DIP-8 | 8 pin DIP IC Socket Adaptor Solder Type (taydaelectronics.com)
E2, E3, E4, E5, E6, E7, E8, E9, E10 | IC Socket | 9 | DIP-14 | 14 pin DIP IC Socket Adaptor Solder Type (taydaelectronics.com)
EC1, EC2 | IC Socket | 2 | DIP-20 | 20 pin DIP IC Socket Adaptor Solder Type (taydaelectronics.com)
External Parts
K1, K2 | Alu Pot Knobs 22mm | 2 | 6.35mm shaft | Aluminum Knob with Delta Mark (taydaelectronics.com)
K1, K2, K3, K4 | Black Pot Knobs slim | 4 | knurled shaft | 10 Pcs Black Plastic Potentiometer Rotary Control Knobs Caps for 6mm Dia Sh'yg 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
K5, K6, K7, K8, K9, K10, K11, K12, K13 | Black Switch Caps | 9 |  | Push Button Switch Caps Black Color 6x5mm (taydaelectronics.com) | other colours than black availiable at Tayda
W1,W2 | IDC Ribboncable 10 Pin | 2 |  | 10 Conductor AWG 28 Flat Ribbon Cable 1FT (30cm) (taydaelectronics.com)
J34, J35, J36, J37 | IDC Header Female 5x2 Pin | 4 |  | IDC Socket Connector 2.54mm 2*4 Pin (taydaelectronics.com)
